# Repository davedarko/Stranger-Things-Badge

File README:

10cm x 10cm badge design

the idea is :
badge that communicates with others by broadcasting a message
every receiving badge with spell out the received message

atmega328 with touch interface?

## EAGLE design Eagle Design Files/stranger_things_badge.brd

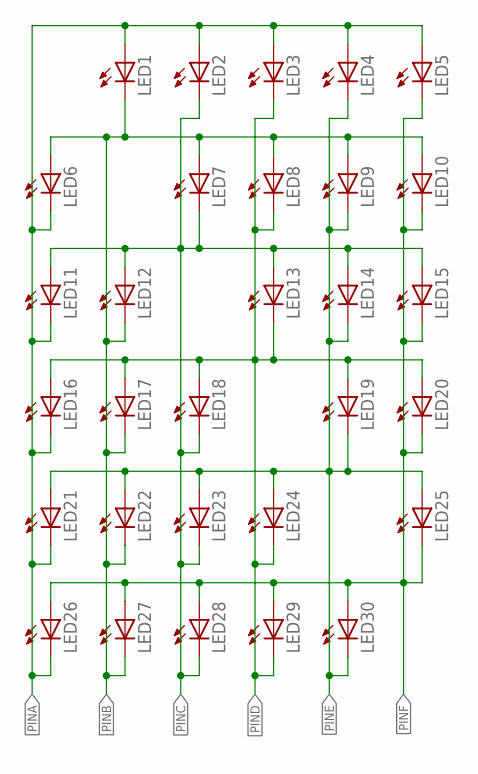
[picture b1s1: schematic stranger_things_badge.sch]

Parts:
LED1, LED11, LED20, LED24: LEDCHIPLED_0805; CHIPLED_0805
LED2, LED3, LED4, LED5, LED6, LED7, LED8, LED9, LED10, LED12, LED13, LED14, LED15, LED16, LED17, LED18, LED19, LED21, LED22, LED23, LED25, LED26, LED27, LED28, LED29, LED30: LEDSTRANGELED; CHIPLED_0805_BS

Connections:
PINA: LED1.A, LED2.A, LED3.A, LED4.A, LED5.A, LED6.C, LED11.C, LED16.C, LED21.C, LED26.C
PINB: LED1.C, LED6.A, LED7.A, LED8.A, LED9.A, LED10.A, LED12.C, LED17.C, LED22.C, LED27.C
PINC: LED2.C, LED7.C, LED11.A, LED12.A, LED13.A, LED14.A, LED15.A, LED18.C, LED23.C, LED28.C
PIND: LED3.C, LED8.C, LED13.C, LED16.A, LED17.A, LED18.A, LED19.A, LED20.A, LED24.C, LED29.C
PINE: LED4.C, LED9.C, LED14.C, LED19.C, LED21.A, LED22.A, LED23.A, LED24.A, LED25.A, LED30.C
PINF: LED5.C, LED10.C, LED15.C, LED20.C, LED25.C, LED26.A, LED27.A, LED28.A, LED29.A, LED30.A

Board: 2 copper layers, 30 parts (30 on the bottom side), 6 nets, no tracks yet.

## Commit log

2018-02-23 badge concept
2018-02-23 docs
2018-02-23 readme
2018-02-23 ahhh
